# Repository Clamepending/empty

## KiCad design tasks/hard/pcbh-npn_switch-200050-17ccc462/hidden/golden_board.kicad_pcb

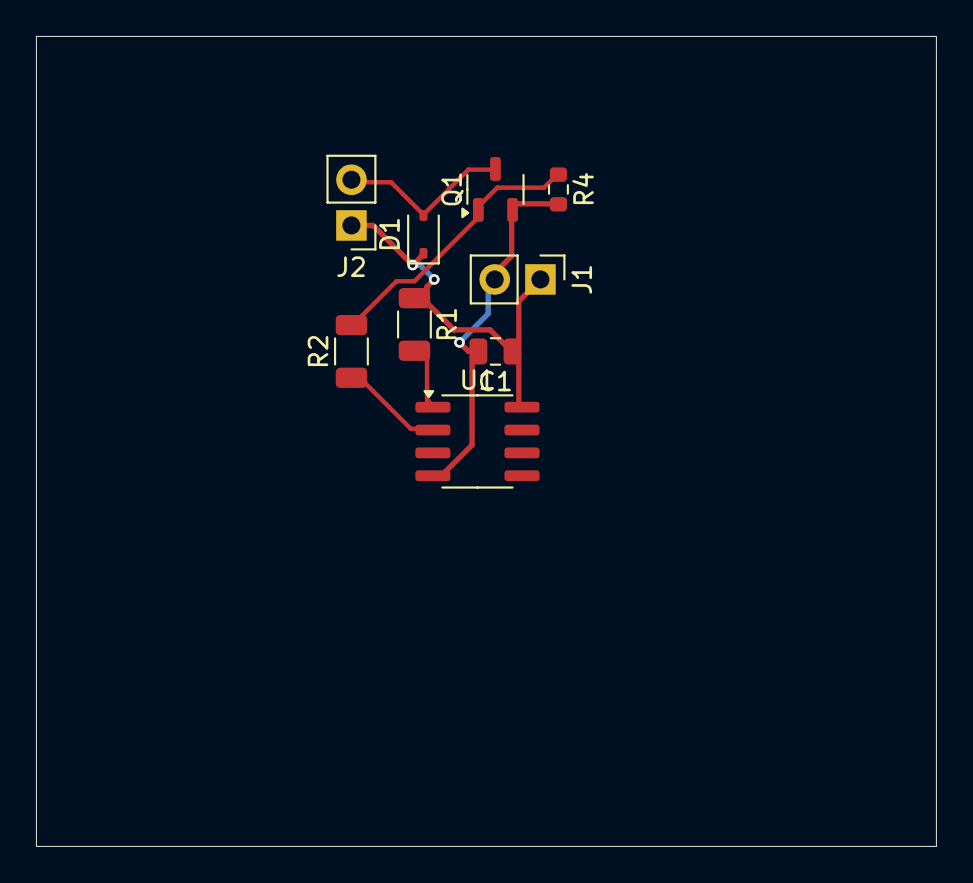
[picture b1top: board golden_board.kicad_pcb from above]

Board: 2 copper layers, 50.0 x 45.0 mm, 9 parts (0 on the bottom side), 6 nets.

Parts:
C1: 1u; C_0805_2012Metric
D1: D_SOD-323
J1, J2: PinHeader_1x02_P2.54mm_Vertical
Q1: SOT-23-3
R1: 6.2k; R_1206_3216Metric
R2: 750; R_1206_3216Metric
R4: 62k; R_0603_1608Metric
U1: SOIC-8_3.9x4.9mm_P1.27mm

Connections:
+5V: C1.1, D1.1, J1.1, J2.1, R1.1, U1.8
BASE: Q1.1, R2.2, R4.1
CTRL: R2.1, U1.2
GND: C1.2, J1.2, Q1.2, R4.2, U1.4
NRST: R1.2, U1.1
SW: D1.2, J2.2, Q1.3

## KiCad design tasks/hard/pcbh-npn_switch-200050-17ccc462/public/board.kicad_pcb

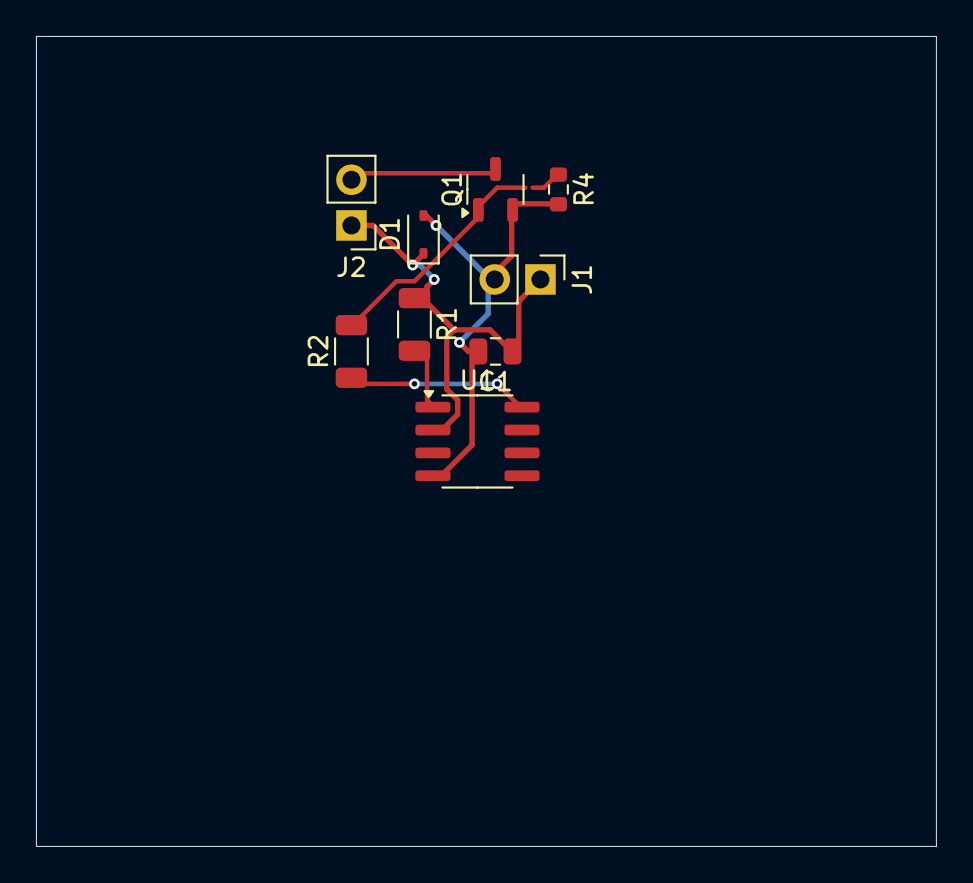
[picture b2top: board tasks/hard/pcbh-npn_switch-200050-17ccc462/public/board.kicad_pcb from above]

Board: 2 copper layers, 50.0 x 45.0 mm, 9 parts (0 on the bottom side), 6 nets.

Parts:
C1: 1u; C_0805_2012Metric
D1: D_SOD-323
J1, J2: PinHeader_1x02_P2.54mm_Vertical
Q1: SOT-23-3
R1: 6.2k; R_1206_3216Metric
R2: 750; R_1206_3216Metric
R4: 62k; R_0603_1608Metric
U1: SOIC-8_3.9x4.9mm_P1.27mm

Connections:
+5V: C1.1, D1.1, J1.1, J2.1, R1.1, U1.2
BASE: Q1.1, R2.2, R4.1
CTRL: R2.1, U1.8
GND: C1.2, D1.2, J1.2, Q1.2, R4.2, U1.4
NRST: R1.2, U1.1
SW: J2.2, Q1.3

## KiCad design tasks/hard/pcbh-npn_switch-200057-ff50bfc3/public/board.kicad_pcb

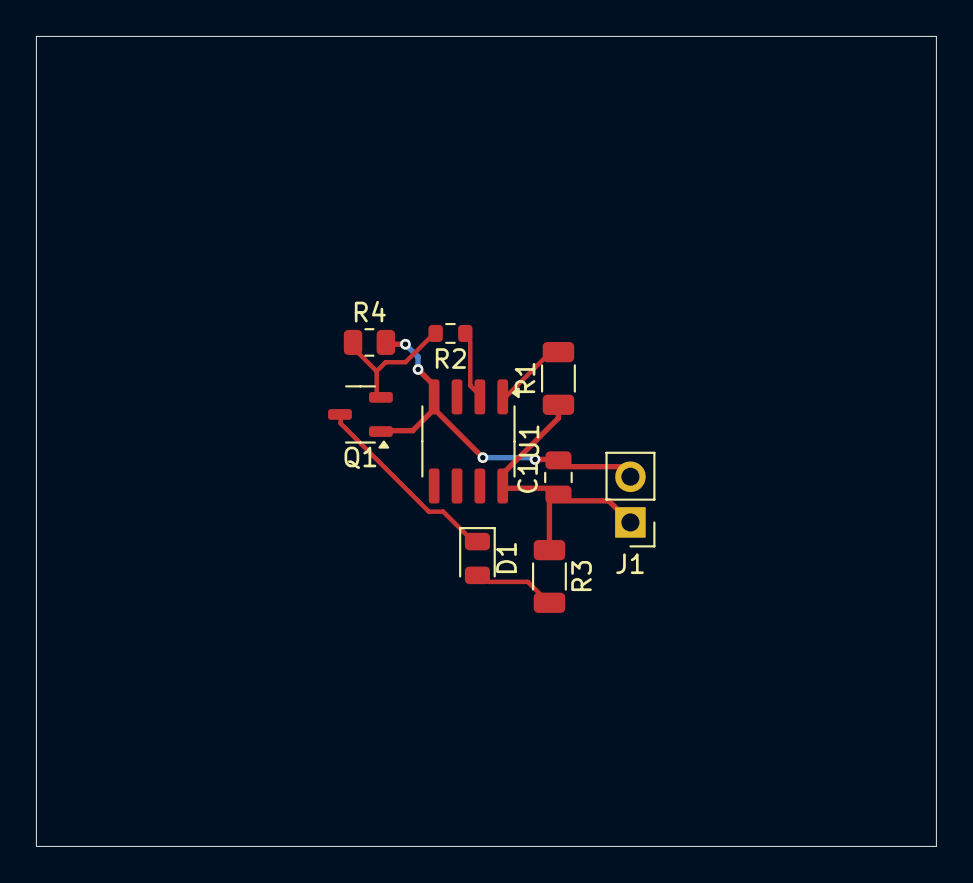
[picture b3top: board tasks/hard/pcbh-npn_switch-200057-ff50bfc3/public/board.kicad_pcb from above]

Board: 2 copper layers, 50.0 x 45.0 mm, 9 parts (0 on the bottom side), 7 nets.

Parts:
C1: 1u; C_0805_2012Metric
D1: LED_0805_2012Metric
J1: PinHeader_1x02_P2.54mm_Vertical
Q1: SOT-23-3
R1: 27k; R_1206_3216Metric
R2: 8.9k; R_0603_1608Metric
R3: 180; R_1206_3216Metric
R4: 75k; R_0805_2012Metric
U1: SOIC-8_3.9x4.9mm_P1.27mm

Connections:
+5V: C1.1, J1.1, R1.1, R3.1, U1.8
BASE: Q1.2, R2.2, R4.1
CTRL: R2.1, U1.2
GND: C1.2, J1.2, Q1.1, R4.2, U1.4
LED_A: D1.2, R3.2
NRST: R1.2, U1.1
SW: D1.1, Q1.3
